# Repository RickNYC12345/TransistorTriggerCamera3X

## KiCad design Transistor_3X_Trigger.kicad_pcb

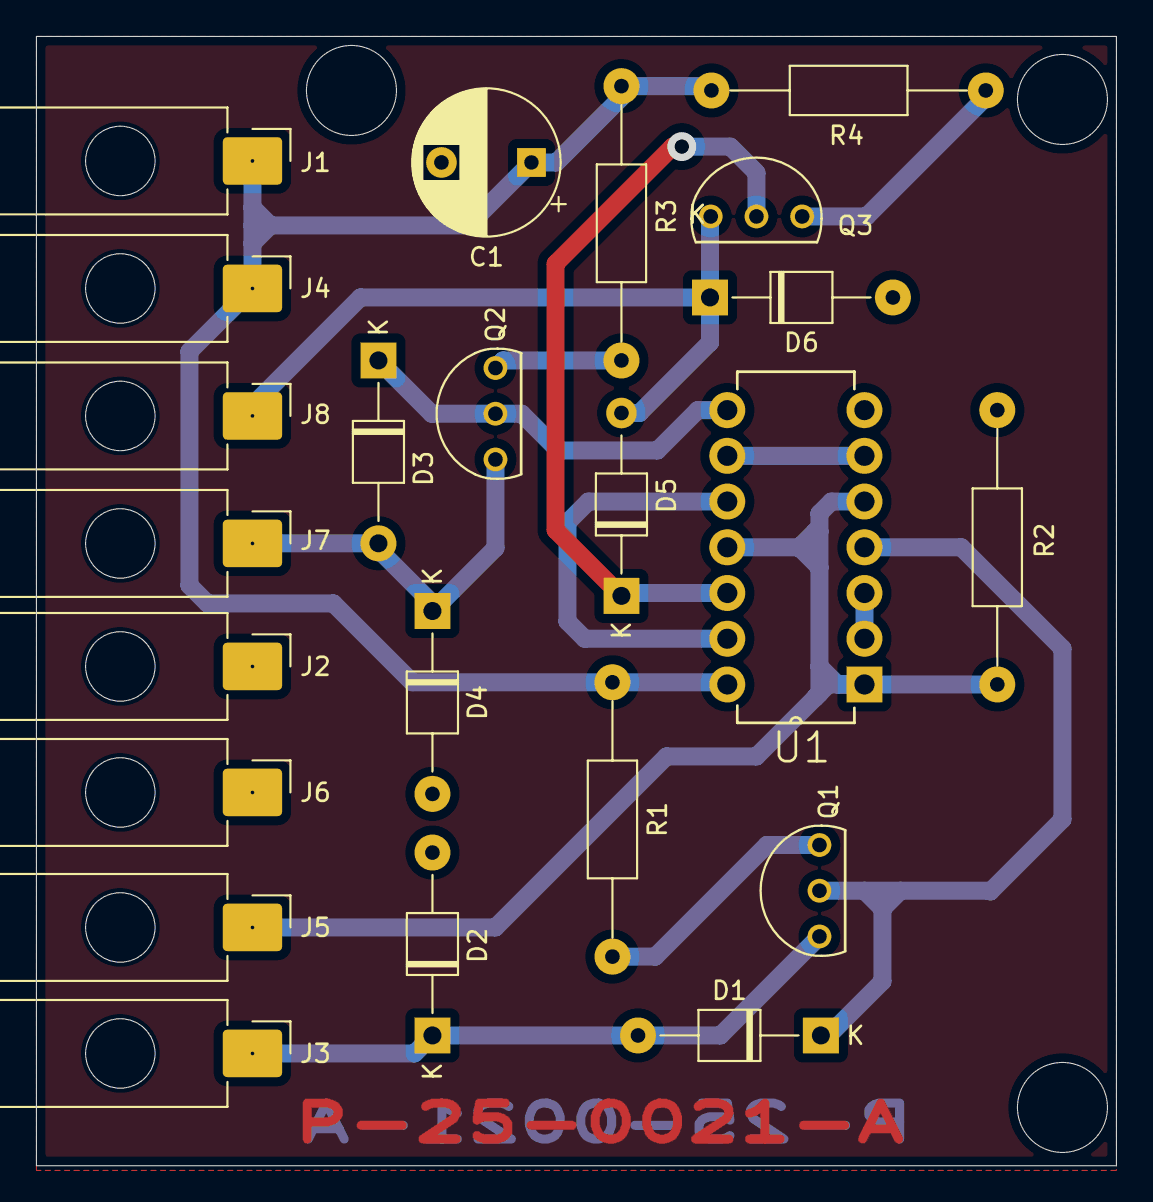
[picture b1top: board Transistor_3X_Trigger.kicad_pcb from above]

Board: 2 copper layers, 60.0 x 62.7 mm, 23 parts (0 on the bottom side), 15 nets.

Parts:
C1: 100nF; CP_Radial_D8.0mm_P5.00mm
D1, D3, D5: 4148 type; D_T-1_P10.16mm_Horizontal
D2, D4, D6: D_Zener 5V; D_T-1_P10.16mm_Horizontal
J1, J2, J3, J4, J5, J6, J7, J8: Conn_01x01_Pin; TE_MATE-N-LOK_1-794374-x_1x01_P4.14mm_Horizontal
Q1, Q2, Q3: 2N4401; TO92
R1, R3, R4: 10; R_Axial_DIN0207_L6.3mm_D2.5mm_P15.24mm_Horizontal
R2: 10k; R_Axial_DIN0207_L6.3mm_D2.5mm_P15.24mm_Horizontal
U1: 74HC14N_652; DIP254P762X420-14

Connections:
+5V: C1.1, J1.1, J4.1, R1.1, R3.1, R4.1, U1.14 (VCC)
/OptBoxInput: J5.1, R2.1, U1.1 (1A), U1.5 (3A), U1.11 (5A)
/SchmidtLink1: U1.2 (1Y), U1.3 (2A)
/SchmidtLink2: U1.6 (3Y), U1.9 (4A)
/SchmidtLink3: U1.10 (5Y), U1.13 (6A)
/transistors1/Collector1: Q1.3, R1.2
/transistors1/Collector2: Q2.3, R3.2
/transistors1/Collector3: Q3.3, R4.2
/transistors1/Output1: D1.2 (A), D2.1 (K), J3.1, Q1.1
/transistors1/Output2: D3.2 (A), D4.1 (K), J7.1, Q2.1
/transistors1/Output3: D5.2 (A), D6.1 (K), J8.1, Q3.1
GND: C1.2, D2.2 (A), D4.2 (A), D6.2 (A), J2.1, J6.1, R2.2, U1.7 (GND)
Trig1: D1.1 (K), Q1.2, U1.4 (2Y)
Trig2: D3.1 (K), Q2.2, U1.8 (4Y)
Trig3: D5.1 (K), Q3.2, U1.12 (6Y)

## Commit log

2025-04-03 extra commits found
